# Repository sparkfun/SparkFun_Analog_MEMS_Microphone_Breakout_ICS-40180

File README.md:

SparkFun MEMS Microphone Breakout ICS-40180
========================================

[*SparkFun MEMS Microphone Breakout (ICS-40180) [BOB-18011]*](https://www.sparkfun.com/products/18011)

The SparkFun MEMS Microphone Breakout (ICS-40180) makes it easy to work with the InvenSense ICS-40180 analog microphone. It includes an OpAmp to bring output of the microphone to a usable level, allowing you to plug directly into an ADC on a microcontroller or something like the SparkFun Spectrum Shield. In addition to amplifying the signal, the OpAmp adds a bias voltage of 1/2 VCC. With sound sources such as normal talking voice a few feet away from the microphone, the AUD output signal will be at about 200mV peak-to-peak. Also note, this low profile microphone has its port on the bottom side, so the microphone can be mounted flush to the outer surface of your enclosure. This microphone is omni-directional, which means it does a good job of picking up sound sources from all directions.

Repository Contents
-------------------

* **/Documentation** - Data sheets, additional product information
* **/Hardware** - Eagle design files (.brd, .sch)
* **/Hardware/Production** - Production panel files (.brd)

Documentation
--------------
* **[Hookup Guide]()** - Basic hookup guide for the SparkFun MEMS microphone breakout.

License Information
-------------------

This product is _**open source**_! 

Please review the LICENSE.md file for license information. 

If you have any questions or concerns on licensing, please contact technical support on our [SparkFun forums](https://forum.sparkfun.com/viewforum.php?f=152).

Distributed as-is; no warranty is given.

- Your friends at SparkFun.

_<COLLABORATION CREDIT>_

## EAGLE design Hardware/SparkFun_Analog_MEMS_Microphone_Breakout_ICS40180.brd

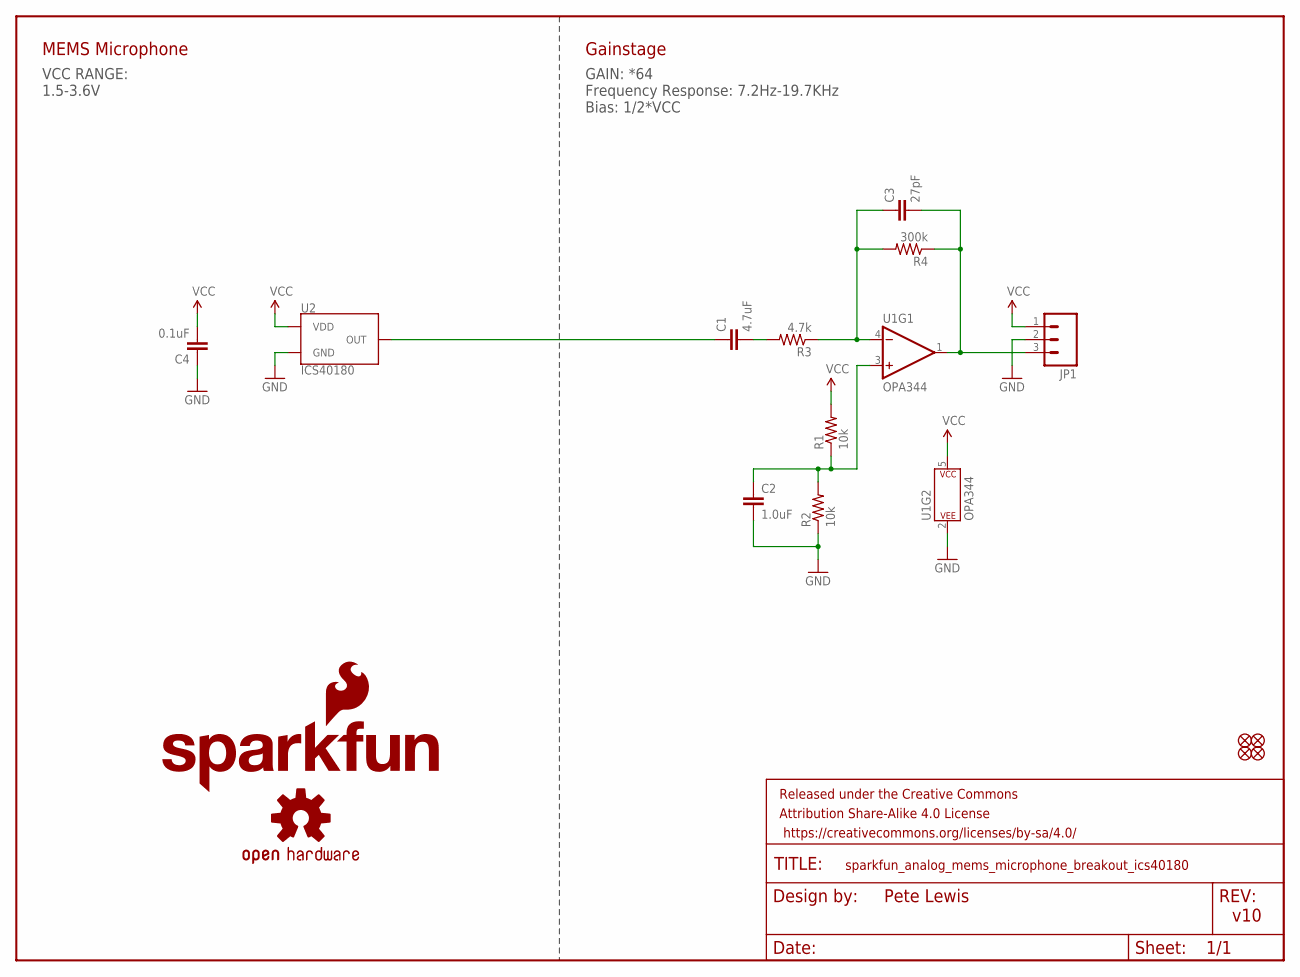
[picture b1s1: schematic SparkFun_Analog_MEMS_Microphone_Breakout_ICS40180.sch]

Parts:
C1: 4.7uF; 0603
C2: 1.0uF; 0603
C3: 27pF; 0603
C4: 0.1uF; 0603
FD1, FD2, FD3, FD4: FIDUCIALUFIDUCIAL; FIDUCIAL-MICRO
FRAME2: FRAME-LETTER; CREATIVE_COMMONS
JP1: CONN_031X03_NO_SILK; 1X03_NO_SILK
LOGO1: SFE_LOGO_FLAME.1_INCH; SFE_LOGO_FLAME_.1
LOGO2: OSHW-LOGOMINI; OSHW-LOGO-MINI
R1, R2: 10k; 0603
R3: 4.7k; 0603
R4: 300k; 0603
U1: OPA344; SOT23-5
U2: ICS40180

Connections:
AUD: C3.2, JP1.3, R4.1, U1.1 (OUT)
GND: C2.2, C4.1, JP1.2, R2.1, U1.2 (P$V-), U2.2 (GND), U2.3 (GND), U2.4 (GND)
unnamed: C1.1, U2.1 (OUT)
unnamed: C3.1, R3.1, R4.2, U1.4 (-IN)
unnamed: C1.2, R3.2
unnamed: C2.1, R1.1, R2.2, U1.3 (+IN)
VCC: C4.2, JP1.1, R1.2, U1.5 (P$V+), U2.5 (VDD)

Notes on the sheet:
v10
Pete Lewis
VCC RANGE: 1.5-3.6V
MEMS Microphone
Gainstage
GAIN: *64 Frequency Response: 7.2Hz-19.7KHz Bias: 1/2*VCC

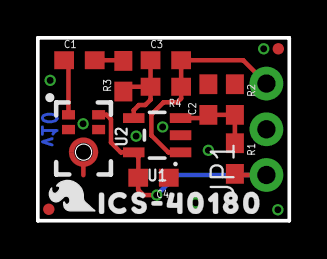
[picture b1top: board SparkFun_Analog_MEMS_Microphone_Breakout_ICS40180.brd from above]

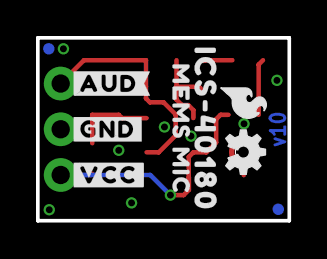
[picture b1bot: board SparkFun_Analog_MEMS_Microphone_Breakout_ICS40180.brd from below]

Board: 2 copper layers, 14.0 x 10.2 mm, 25 parts (9 on the bottom side), 7 nets.

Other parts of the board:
LOGO3: SFE_LOGO_FLAME.1_INCH; SFE_LOGO_FLAME_.1
U$1, U$6: ICS#401800
U$2: MEMS_MIC0
U$3: #GND#0
U$4: #VCC#0
U$5: #AUD#0

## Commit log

2021-02-16 initial layout
2021-02-24 changed label to fish flag output on AUD pin
    added fiducials
2021-02-26 Moved passives for tighter layout
    -Moved passives to tighten up traces near + and - inputs on op amp.
    -Added mic model # and flame to top silk
    -Added measures
2021-03-01 datasheet
2021-03-01 Changed values to extend freq response
    -Changes passives to extend frequency rolloffs on the opamp circuit. It's not 7.2Hz-19.7KHz, which better matches the capabilities of the new mic.
    -Added SparkFun "name" logo to schematic - note, I copied vectors from library so it isn't a proper symbol/device.
    -rearranged schematic and labeled "mic" and "gainstage" sections
    -Capitalized the S in MEMS on the bottom silk.
    -Made measures text size all the same at 0.05inch
2021-03-01 capitalizing S in MEMS file name
2021-03-01 name update
2021-03-01 checklist updates
    -rearranged tName for assembly sheet
    -removed one stub
    -nudge a trace to allow better gnd flow.
2021-03-01 Reduced paste on the mic FP
    -reduced both on the GND ring and the other 4 rectangular pads.
2021-03-01 production panel gerbers v10
2021-03-02 removed one measure that was unnecessary
    -we don't really need to show measure for each individual 0.1inch header, the spacing can be assumed as pitch of headers.
2021-04-19 OPA344 datasheet added to documents directory
2021-06-16 Migrating mic and VCC/GNDs to latest eagle libraries
    -Doesn't change design at all, but just makes it cleaner/easier to know where the devices live in our main eagle libraries repo.

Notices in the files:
parts and their libraries:
SparkFun-Resistors: Licensing: Creative Commons ShareAlike 4.0 International - https://creativecommons.org/licenses/by-sa/4.0
SparkFun-Aesthetics: Released under the Creative Commons Attribution Share-Alike 4.0 License
SparkFun-Aesthetics: https://creativecommons.org/licenses/by-sa/4.0
